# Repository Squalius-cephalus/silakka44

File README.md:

# Silakka44

Silakka44 is a RP2040 based 44-key column staggered split keyboard. PCB uses hotswap sockets. Design is inpired from REVIUNG41 and Corne keyboards.

PCB is designed for MX style key switches. Current top plate only supports MX style switches. 5-pin switches is supported.

[QMK](https://github.com/qmk/qmk_firmwarehttp:// "QMK") and [Vial](https://github.com/vial-kb/vial-qmk "Vial") firmwares has very barebones key mapping. Good for quick testing.

You can find build guide [here.](https://github.com/Squalius-cephalus/silakka44/blob/main/buildguide/README.md "here.")

PCB design uses footprints from [ScottoKeebs](https://github.com/joe-scotto/scottokeebs/tree/main/Extras/ScottoKicad "ScottoKeebs") and [kbd library.](https://github.com/foostan/kbd "kbd library.")

### Bugs
Sometimes the encoder buttons are "stuck" when the keyboard is connected to the computer. Pressing those once fixes the problem.

### TODO
1. Redo traces
2. Fix bugs

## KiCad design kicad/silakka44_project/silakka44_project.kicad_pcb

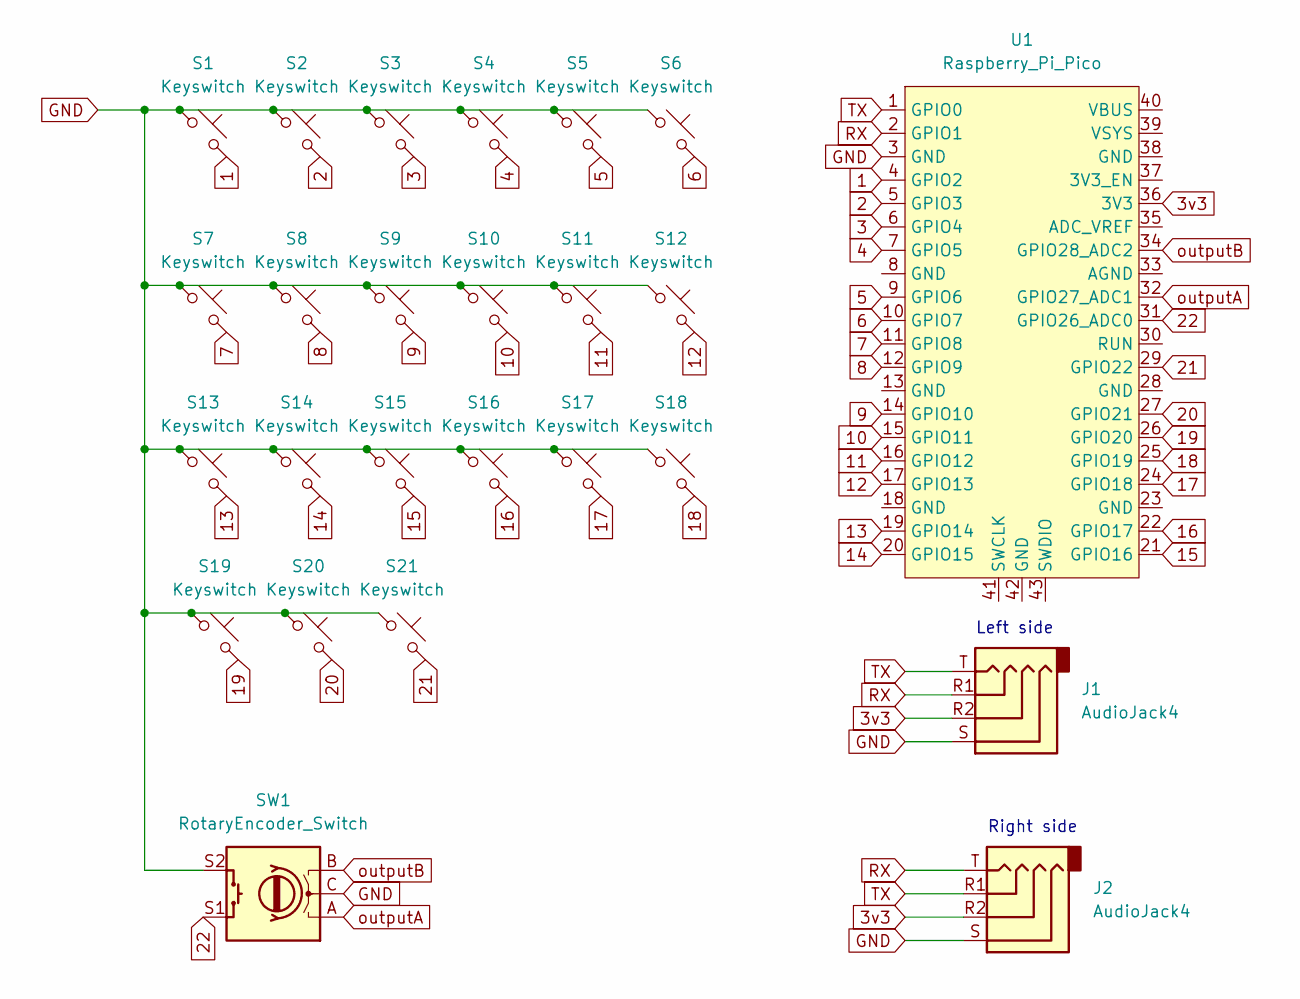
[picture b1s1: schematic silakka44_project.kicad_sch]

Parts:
J1, J2: AudioJack4; Jack_3.5mm_PJ320D_Horizontal
S1, S2, S3, S4, S5, S6, S7, S8, S9, S10, S11, S12, S13, S14, S15, S16, S17, S18, S19, S20, S21: Keyswitch; CherryMX_MidHeight_Hotswap
SW1: RotaryEncoder_Switch; RotaryEncoder_EC11
U1: Raspberry_Pi_Pico

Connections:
1: S1.2, U1.4 (GPIO2)
2: S2.2, U1.5 (GPIO3)
3: S3.2, U1.6 (GPIO4)
3v3: J1.R2, J2.R2, U1.36 (3V3)
4: S4.2, U1.7 (GPIO5)
5: S5.2, U1.9 (GPIO6)
6: S6.2, U1.10 (GPIO7)
7: S7.2, U1.11 (GPIO8)
8: S8.2, U1.12 (GPIO9)
9: S9.2, U1.14 (GPIO10)
10: S10.2, U1.15 (GPIO11)
11: S11.2, U1.16 (GPIO12)
12: S12.2, U1.17 (GPIO13)
13: S13.2, U1.19 (GPIO14)
14: S14.2, U1.20 (GPIO15)
15: S15.2, U1.21 (GPIO16)
16: S16.2, U1.22 (GPIO17)
17: S17.2, U1.24 (GPIO18)
18: S18.2, U1.25 (GPIO19)
19: S19.2, U1.26 (GPIO20)
20: S20.2, U1.27 (GPIO21)
21: S21.2, U1.29 (GPIO22)
22: SW1.S1, U1.31 (GPIO26_ADC0)
GND: J1.S, J2.S, S1.1, S2.1, S3.1, S4.1, S5.1, S6.1, S7.1, S8.1, S9.1, S10.1, S11.1, S12.1, S13.1, S14.1, S15.1, S16.1, S17.1, S18.1, S19.1, S20.1, S21.1, SW1.C, SW1.S2, U1.3 (GND)
RX: J1.R1, J2.T, U1.2 (GPIO1)
TX: J1.T, J2.R1, U1.1 (GPIO0)
outputA: SW1.A, U1.32 (GPIO27_ADC1)
outputB: SW1.B, U1.34 (GPIO28_ADC2)

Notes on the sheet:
Right side
Left side

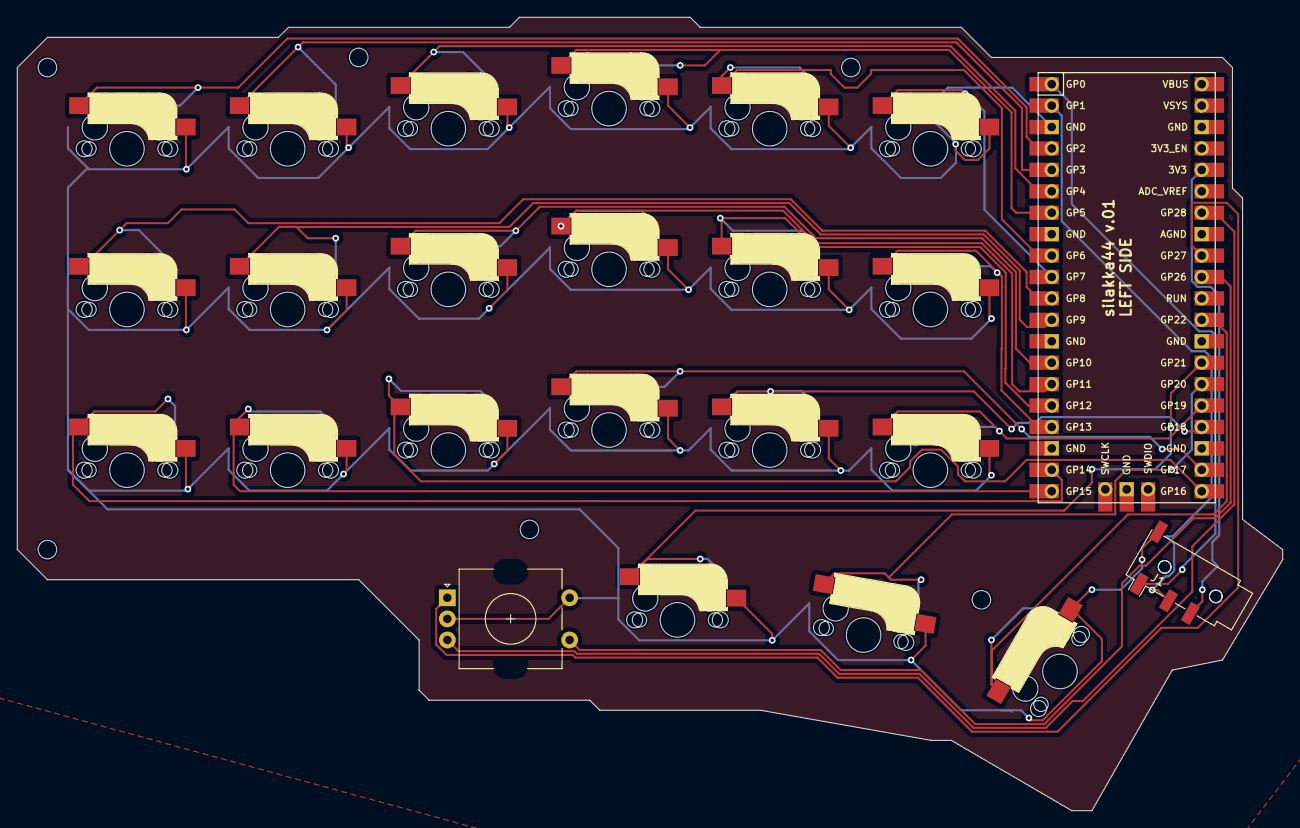
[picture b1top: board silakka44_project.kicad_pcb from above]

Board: 2 copper layers, 150.0 x 94.1 mm, 25 parts (1 on the bottom side), 28 nets.

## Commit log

2024-05-10 Initial commit
    Includes STL files, firmware, KiCAD project and gerber files.
2024-05-13 Updated STL files
2024-05-13 More build guide images
2024-05-13 New build guide for the keyboard
2025-10-03 Rotary encoders fixed
